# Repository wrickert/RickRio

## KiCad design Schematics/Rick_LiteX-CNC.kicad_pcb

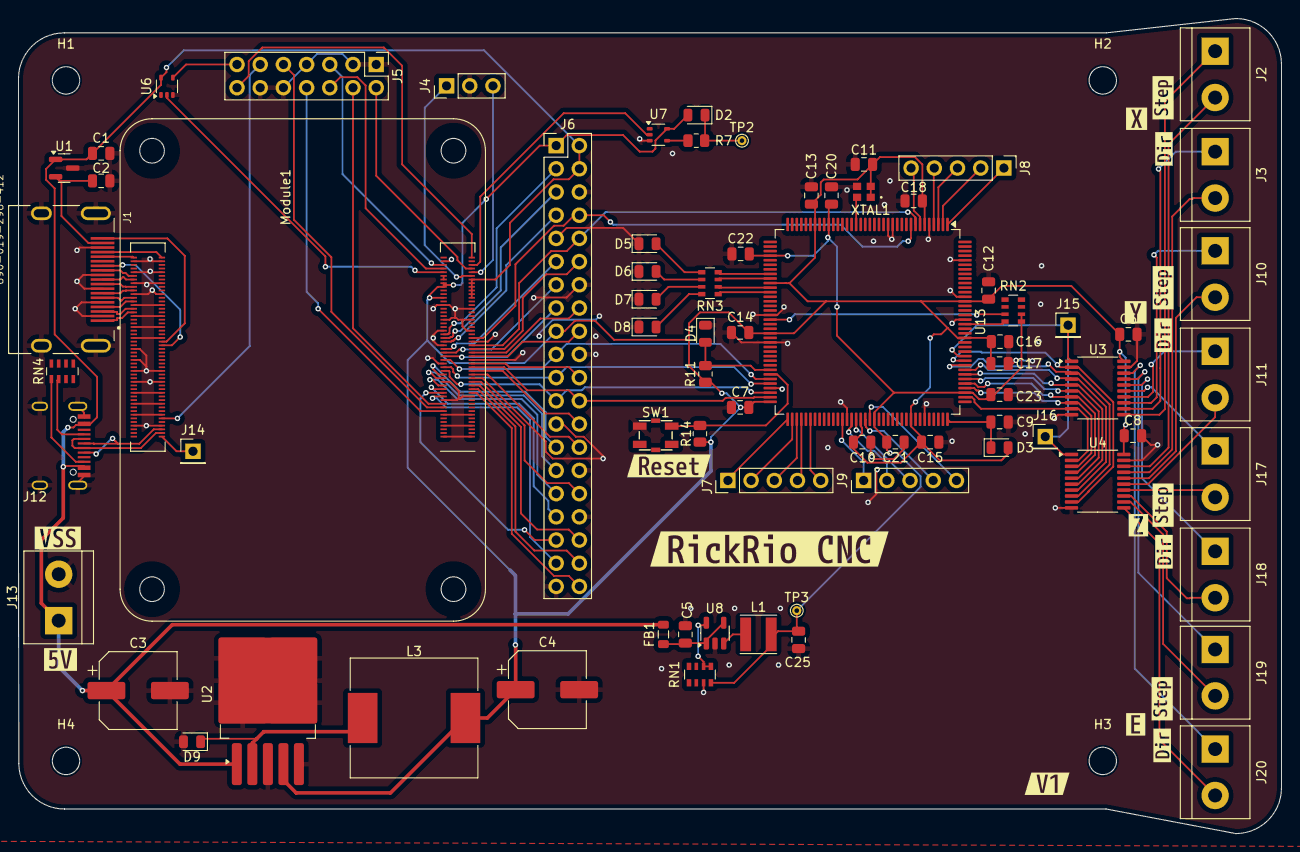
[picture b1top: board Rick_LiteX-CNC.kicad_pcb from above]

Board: 2 copper layers, 138.3 x 89.2 mm, 95 parts (0 on the bottom side), 124 nets.

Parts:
C1, C2: 100n; C_0805_2012Metric
C3, C4: 1000uF; CP_Elec_8x6.9
C5: 4.7u; C_0805_2012Metric
C6, C7, C8, C10, C11, C12, C13, C14, C15, C16, C17, C18, C20, C21, C22, C23: 100nF; C_0805_2012Metric
C9: DNP; C_0805_2012Metric
C25: 22uF; C_0805_2012Metric
D2: LED Red; LED_0805_2012Metric
D3: 800mVf; D_0805_2012Metric
D4, D5, D6, D7, D8: LED_Small; LED_0805_2012Metric
D9: D_Schottky; D_0805_2012Metric
FB1: Ferrite_Bead_Small; L_0805_2012Metric
H1, H2, H3, H4: MountingHole; MountingHole_3mm
J1: 690-019-298-412; EDAC 690-019-298-412
J2, J3, J10, J11, J17, J18, J19, J20: Conn_01x02; TerminalBlock_bornier-2_P5.08mm
J4: Conn_01x03; PinHeader_1x03_P2.54mm_Vertical
J5: Conn_02x07_Odd_Even; PinHeader_2x07_P2.54mm_Vertical
J6: THD-20-R; PinHeader_2x20_P2.54mm_Vertical
J7, J8, J9: Conn_01x05; PinHeader_1x05_P2.54mm_Vertical
J12: USB_C_Receptacle; USB_C_Receptical-Jing
J13: Power; TerminalBlock_bornier-2_P5.08mm
J14: Conn_01x01; PinHeader_1x01_P2.54mm_Vertical
J15, J16: En; PinHeader_1x01_P2.54mm_Vertical
L1: 2.2uH; L_Taiyo-Yuden_NR-40xx
L3: 100uH; L_Sunlord_MWSA1205S-R50
Module1: ComputeModule4; Raspberry-Pi-4-Compute-Module
R7: 1k; R_0805_2012Metric
R11: 2k2; R_0805_2012Metric
R14: 10k; R_0805_2012Metric
RN1: 100k; R_Array_Convex_4x0603
RN2: 100; R_Array_Convex_4x0603
RN3: 330; R_Array_Convex_4x0603
RN4: 5.1k; R_Array_Concave_4x0603
SW1: SW_SPST; TS3315A
TP2: TestPoint; TestPoint_THTPad_D1.0mm_Drill0.5mm
TP3: 1.2v; TestPoint_THTPad_D1.0mm_Drill0.5mm
U1: RT9742SNGV; SOT-23
U2: LM2576S-3.3; TO-263-5_TabPin3
U3: 74AC540; TSSOP-20_4.4x6.5mm_P0.65mm
U4: 74AC541; TSSOP-20_4.4x6.5mm_P0.65mm
U6, U7: 74LVC1G07SE-7; SOT-353_SC-70-5
U8: TLV62568DBV; SOT-23-5
U13: ICE40HX4K-TQ144; TQFP-144_20x20mm_P0.5mm
XTAL1: SIT1602BIA73-33E; SON4_SIT1602-7_SIT
kibuzzard-66EC3AFE: G***; kibuzzard-66EC3AFE
kibuzzard-66EC3B2F, kibuzzard-66EC3B2F#2, kibuzzard-66EC3B2F#3, kibuzzard-66EC3B2F#4: G***; kibuzzard-66EC3B2F
kibuzzard-66EC3B4B, kibuzzard-66EC3B4B#2, kibuzzard-66EC3B4B#3, kibuzzard-66EC3B4B#4: G***; kibuzzard-66EC3B4B
kibuzzard-66EC3B6F: G***; kibuzzard-66EC3B6F
kibuzzard-66EC3B7E: G***; kibuzzard-66EC3B7E
kibuzzard-66EC3B08: G***; kibuzzard-66EC3B08
kibuzzard-66EC3B76: G***; kibuzzard-66EC3B76
kibuzzard-66EC3B85: G***; kibuzzard-66EC3B85
kibuzzard-66EC3BBC: G***; kibuzzard-66EC3BBC
kibuzzard-66EC3BC4: G***; kibuzzard-66EC3BC4
kibuzzard-66EC3914: G***; kibuzzard-66EC3914

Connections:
+1V2: C20.2, C21.2, C22.2, C23.2, C25.2, L1.2, RN1.4 (R4.1), RN2.1 (R1.1), RN2.2 (R2.1), TP3.1, U13.27 (VCC), U13.40 (VCC), U13.92 (VCC), U13.111 (VCC)
+5V: C1.1, C3.1, FB1.2, J6.2, J6.4, J12.A4 (VBUS), J12.A9 (VBUS), J12.B4 (VBUS), J12.B9 (VBUS), J13.1, Module1.77 (+5v_(Input)), Module1.79 (+5v_(Input)), Module1.81 (+5v_(Input)), Module1.83 (+5v_(Input)), Module1.85 (+5v_(Input)), Module1.87 (+5v_(Input)), U1.1 (IN), U2.1 (VIN), U6.5 (VCC)
/CNC_IO/Buffer_En: J15.1, J16.1, U3.1 (~G1), U4.1 (~G1), U13.119 (IOT_178)
/CNC_IO/DIR1: U3.8 (A7), U4.3 (A2), U13.112 (IOT_169)
/CNC_IO/DIR2: U3.6 (A5), U4.5 (A4), U13.114 (IOT_171)
/CNC_IO/DIR3: U3.4 (A3), U4.7 (A6), U13.116 (IOT_173)
/CNC_IO/DIR4: U3.2 (A1), U4.9 (A8), U13.118 (IOT_177)
/CNC_IO/ST1: U3.9 (A8), U4.2 (A1), U13.110 (IOT_168)
/CNC_IO/ST2: U3.7 (A6), U4.4 (A3), U13.113 (IOT_170)
/CNC_IO/ST3: U3.5 (A4), U4.6 (A5), U13.115 (IOT_172)
/CNC_IO/ST4: U3.3 (A2), U4.8 (A7), U13.117 (IOT_174)
/Power/D+: J12.A6 (D+), J12.B6 (D+), Module1.105 (USB2_P)
/Power/D-: J12.A7 (D-), J12.B7 (D-), Module1.103 (USB2_N)
/Raspberry Pi CM4/+1.8v: Module1.88 (+1.8v_(Output)), Module1.90 (+1.8v_(Output))
/Raspberry Pi CM4/AIN0: J5.5, Module1.96 (AnalogIP1)
/Raspberry Pi CM4/AIN1: J5.6, Module1.94 (AnalogIP0)
/Raspberry Pi CM4/BT_nDis: J4.3, Module1.91 (BT_nDisable)
/Raspberry Pi CM4/EEPROM_nWP: J5.4, Module1.20 (EEPROM_nWP)
/Raspberry Pi CM4/GLOBAL_EN: J5.14, Module1.99 (Global_EN)
/Raspberry Pi CM4/GPIO2: J6.3, Module1.58 (GPIO2)
/Raspberry Pi CM4/GPIO3: J6.5, Module1.56 (GPIO3)
/Raspberry Pi CM4/GPIO4: J6.7, Module1.54 (GPIO4)
/Raspberry Pi CM4/GPIO5: J6.29, Module1.34 (GPIO5)
/Raspberry Pi CM4/GPIO6: J6.31, Module1.30 (GPIO6)
/Raspberry Pi CM4/GPIO7: J6.26, Module1.37 (GPIO7)
/Raspberry Pi CM4/GPIO8: J6.24, Module1.39 (GPIO8), U13.71 (IOB_108_SS)
/Raspberry Pi CM4/GPIO9: J6.21, Module1.40 (GPIO9), U13.68 (IOB_106_SDI)
/Raspberry Pi CM4/GPIO10: J6.19, Module1.44 (GPIO10), U13.67 (IOB_105_SDO)
/Raspberry Pi CM4/GPIO11: J6.23, Module1.38 (GPIO11), U13.70 (IOB_107_SCK)
/Raspberry Pi CM4/GPIO12: J6.32, Module1.31 (GPIO12)
/Raspberry Pi CM4/GPIO13: J6.33, Module1.28 (GPIO13)
/Raspberry Pi CM4/GPIO14: J6.8, Module1.55 (GPIO14), U13.9 (IOL_5A)
/Raspberry Pi CM4/GPIO15: J6.10, Module1.51 (GPIO15), U13.8 (IOL_4B)
/Raspberry Pi CM4/GPIO16: J6.36, Module1.29 (GPIO16)
/Raspberry Pi CM4/GPIO17: J6.11, Module1.50 (GPIO17)
/Raspberry Pi CM4/GPIO18: J6.12, Module1.49 (GPIO18)
/Raspberry Pi CM4/GPIO19: J6.35, Module1.26 (GPIO19)
/Raspberry Pi CM4/GPIO20: J6.38, Module1.27 (GPIO20)
/Raspberry Pi CM4/GPIO21: J6.40, Module1.25 (GPIO21)
/Raspberry Pi CM4/GPIO22: J6.15, Module1.46 (GPIO22)
/Raspberry Pi CM4/GPIO23: J6.16, Module1.47 (GPIO23)
/Raspberry Pi CM4/GPIO24: J6.18, Module1.45 (GPIO24)
/Raspberry Pi CM4/GPIO25: J6.22, Module1.41 (GPIO25)
/Raspberry Pi CM4/GPIO26: J6.37, Module1.24 (GPIO26)
/Raspberry Pi CM4/GPIO27: J6.13, Module1.48 (GPIO27)
/Raspberry Pi CM4/HDMI0_CEC: J1.13 (CEC), Module1.151 (HDMI0_CEC)
/Raspberry Pi CM4/HDMI0_CK_N: J1.12 (CK-), Module1.190 (HDMI0_CLK_N)
/Raspberry Pi CM4/HDMI0_CK_P: J1.10 (CK+), Module1.188 (HDMI0_CLK_P)
/Raspberry Pi CM4/HDMI0_D0_N: J1.9 (D0-), Module1.184 (HDMI0_TX0_N)
/Raspberry Pi CM4/HDMI0_D0_P: J1.7 (D0+), Module1.182 (HDMI0_TX0_P)
/Raspberry Pi CM4/HDMI0_D1_N: J1.6 (D1-), Module1.178 (HDMI0_TX1_N)
/Raspberry Pi CM4/HDMI0_D1_P: J1.4 (D1+), Module1.176 (HDMI0_TX1_P)
/Raspberry Pi CM4/HDMI0_D2_N: J1.3 (D2-), Module1.172 (HDMI0_TX2_N)
/Raspberry Pi CM4/HDMI0_D2_P: J1.1 (D2+), Module1.170 (HDMI0_TX2_P)
/Raspberry Pi CM4/HDMI0_HOTPLUG: J1.19 (HPD/HEAC-), Module1.153 (HDMI0_HOTPLUG)
/Raspberry Pi CM4/HDMI0_SCL: J1.15 (SCL), Module1.200 (HDMI0_SCL)
/Raspberry Pi CM4/HDMI0_SDA: J1.16 (SDA), Module1.199 (HDMI0_SDA)
/Raspberry Pi CM4/HDMI_5v: C2.1, J1.18 (+5V), U1.2 (OUT)
/Raspberry Pi CM4/ID_SC: J6.28, Module1.35 (ID_SC)
/Raspberry Pi CM4/ID_SD: J6.27, Module1.36 (ID_SD)
/Raspberry Pi CM4/RUN_PG: Module1.92 (RUN_PG), U6.2
/Raspberry Pi CM4/SYNC_IN: J5.8, Module1.16 (Ethernet_SYNC_IN(1.8v))
/Raspberry Pi CM4/SYNC_OUT: J5.9, Module1.18 (Ethernet_SYNC_OUT(1.8v))
/Raspberry Pi CM4/TV_OUT: J5.11, Module1.111 (VDAC_COMP)
/Raspberry Pi CM4/WL_nDis: J4.1, Module1.89 (WiFi_nDisable)
/Raspberry Pi CM4/nPWR_LED: Module1.95 (nPI_LED_PWR), U7.2
/Raspberry Pi CM4/nRPIBOOT: J5.2, Module1.93 (nRPIBOOT)
A: J7.1, U13.73 (IOR_109)
B: J7.2, U13.74 (IOR_110)
C: J7.3, U13.75 (IOR_111)
CRESET: R14.2, SW1.2 (B), U13.66 (~CRESET)
Clock: U13.21 (IOL_14A_GBIN6), XTAL1.3 (OUT)
D: J7.4, U13.76 (IOR_112)
DIRo1: J3.2, U4.17 (Y2)
DIRo2: J11.2, U4.15 (Y4)
DIRo3: J18.2, U4.13 (Y6)
DIRo4: J20.2, U4.11 (Y8)
E: J7.5, U13.78 (IOR_114)
F: J8.1, U13.1 (IOL_2A)
G: J8.2, U13.2 (IOL_2B)
H: J8.3, U13.3 (IOL_3A)
I: J8.4, U13.4 (IOL_3B)
J: J8.5, U13.7 (IOL_4A)
L: J9.1, U13.85 (IOR_128)
M: J9.2, U13.87 (IOR_136)
N: J9.3, U13.88 (IOR_137)
unnamed: D2.1 (K), R7.1, TP2.1
unnamed: C9.1, D3.1 (K), U13.108 (VPP_2V5)
unnamed: D4.2 (A), R11.2, U13.65 (CDONE)
unnamed: D5.2 (A), RN3.5 (R4.2)
unnamed: D6.2 (A), RN3.6 (R3.2)
unnamed: D7.2 (A), RN3.7 (R2.2)
unnamed: D8.2 (A), RN3.8 (R1.2)
unnamed: D9.1 (K), L3.1, U2.2 (OUT)
unnamed: J5.13, U6.4
unnamed: J12.A5 (CC1), RN4.2 (R2.1)
unnamed: J12.B5 (CC2), RN4.1 (R1.1)
unnamed: J14.1, Module1.101 (USB_OTG_ID)
unnamed: R7.2, U7.4
unnamed: RN1.5 (R4.2), RN1.6 (R3.2), U8.5 (FB)
unnamed: RN2.8 (R1.2), U13.126 (VCCPLL1)
unnamed: RN2.7 (R2.2), U13.54 (VCCPLL0)
unnamed: RN3.1 (R1.1), U13.48 (IOB_80)
unnamed: RN3.2 (R2.1), U13.47 (IOB_79)
unnamed: RN3.3 (R3.1), U13.45 (IOB_73)
unnamed: RN3.4 (R4.1), U13.44 (IOB_72)
unnamed: C5.1, FB1.1, U8.1 (EN), U8.4 (VIN)
unnamed: L1.1, U8.3 (SW)
O: J9.4, U13.90 (IOR_138)
P: J9.5, U13.91 (IOR_139)
STo1: J2.2, U4.18 (Y1)
STo2: J10.2, U4.16 (Y3)
STo3: J17.2, U4.14 (Y5)
STo4: J19.2, U4.12 (Y7)
VCC: C4.1, C6.1, C7.2, C8.1, C10.1, C11.1, C12.2, C13.2, C14.2, C15.2, C16.2, C17.2, C18.2, D2.2 (A), D3.2 (A), J6.1, J6.17, L3.2, Module1.78 (GPIO_VREF(1.8v/3.3v_Input)), Module1.84 (+3.3v_(Output)), Module1.86 (+3.3v_(Output)), R11.1, R14.1, U2.4 (FB), U3.20 (VCC), U4.20 (VCC), U7.5 (VCC), U13.6 (VCCIO_3), U13.30 (VCCIO_3), U13.46 (VCCIO_2), U13.57 (VCCIO_2), U13.72 (VCC_SPI), U13.89 (VCCIO_1), U13.100 (VCCIO_1), U13.123 (VCCIO_0), U13.131 (VCCIO_0), XTAL1.1 (OE/ST/NC), XTAL1.4 (VDD)
VSS: C1.2, C2.2, C3.2, C4.2, C5.2, C6.2, C7.1, C8.2, C9.2, C10.2, C11.2, C12.1, C13.1, C14.1, C15.1, C16.1, C17.1, C18.1, C20.1, C21.1, C22.1, C23.1, C25.1, D4.1 (K), D5.1 (K), D6.1 (K), D7.1 (K), D8.1 (K), D9.2 (A), J1.2 (D2S), J1.5 (D1S), J1.8 (D0S), J1.11 (CKS), J1.17 (GND), J1.SH1 (SH), J1.SH2 (SH), J1.SH3 (SH), J1.SH4 (SH), J4.2, J5.1, J5.3, J5.7, J5.10, J5.12, J6.6, J6.9, J6.14, J6.20, J6.25, J6.30, J6.34, J6.39, J12.A1 (GND), J12.A12 (GND), J12.B1 (GND), J12.B12 (GND), J12.S1 (SHIELD), J13.2, Module1.1 (GND), Module1.2 (GND), Module1.7 (GND), Module1.8 (GND), Module1.13 (GND), Module1.14 (GND), Module1.22 (GND), Module1.23 (GND), Module1.32 (GND), Module1.33 (GND), Module1.42 (GND), Module1.43 (GND), Module1.52 (GND), Module1.53 (GND), Module1.59 (GND), Module1.60 (GND), Module1.65 (GND), Module1.66 (GND), Module1.71 (GND), Module1.74 (GND), Module1.98 (GND), Module1.107 (GND), Module1.108 (GND), Module1.113 (GND), Module1.114 (GND), Module1.119 (GND), Module1.120 (GND), Module1.125 (GND), Module1.126 (GND), Module1.131 (GND), Module1.132 (GND), Module1.137 (GND), Module1.138 (GND), Module1.144 (GND), Module1.150 (GND), Module1.155 (GND), Module1.156 (GND), Module1.161 (GND), Module1.162 (GND), Module1.167 (GND), Module1.168 (GND), Module1.173 (GND), Module1.174 (GND), Module1.179 (GND), Module1.180 (GND), Module1.185 (GND), Module1.186 (GND), Module1.191 (GND), Module1.192 (GND), Module1.197 (GND), Module1.198 (GND), RN1.3 (R3.1), SW1.1 (A), U1.3 (GND), U2.3 (GND), U2.5 (~ON/OFF), U3.10 (VSS), U3.19 (~G2), U4.10 (VSS), U4.19 (~G2), U6.3 (GND), U7.3 (GND), U8.2 (GND), U13.5 (GND), U13.13 (GND), U13.14 (GND), U13.53 (GNDPLL0), U13.59 (GND), U13.69 (GND), U13.86 (GND), U13.103 (GND), U13.127 (GNDPLL1), U13.132 (GND), U13.140 (GND), XTAL1.2 (GND)
~DIR1: J3.1, U3.12 (~Y7)
~DIR2: J11.1, U3.14 (~Y5)
~DIR3: J18.1, U3.16 (~Y3)
~DIR4: J20.1, U3.18 (~Y1)
~ST1: J2.1, U3.11 (~Y8)
~ST2: J10.1, U3.13 (~Y6)
~ST3: J17.1, U3.15 (~Y4)
~ST4: J19.1, U3.17 (~Y2)

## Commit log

2025-01-03 Need to order stencil
